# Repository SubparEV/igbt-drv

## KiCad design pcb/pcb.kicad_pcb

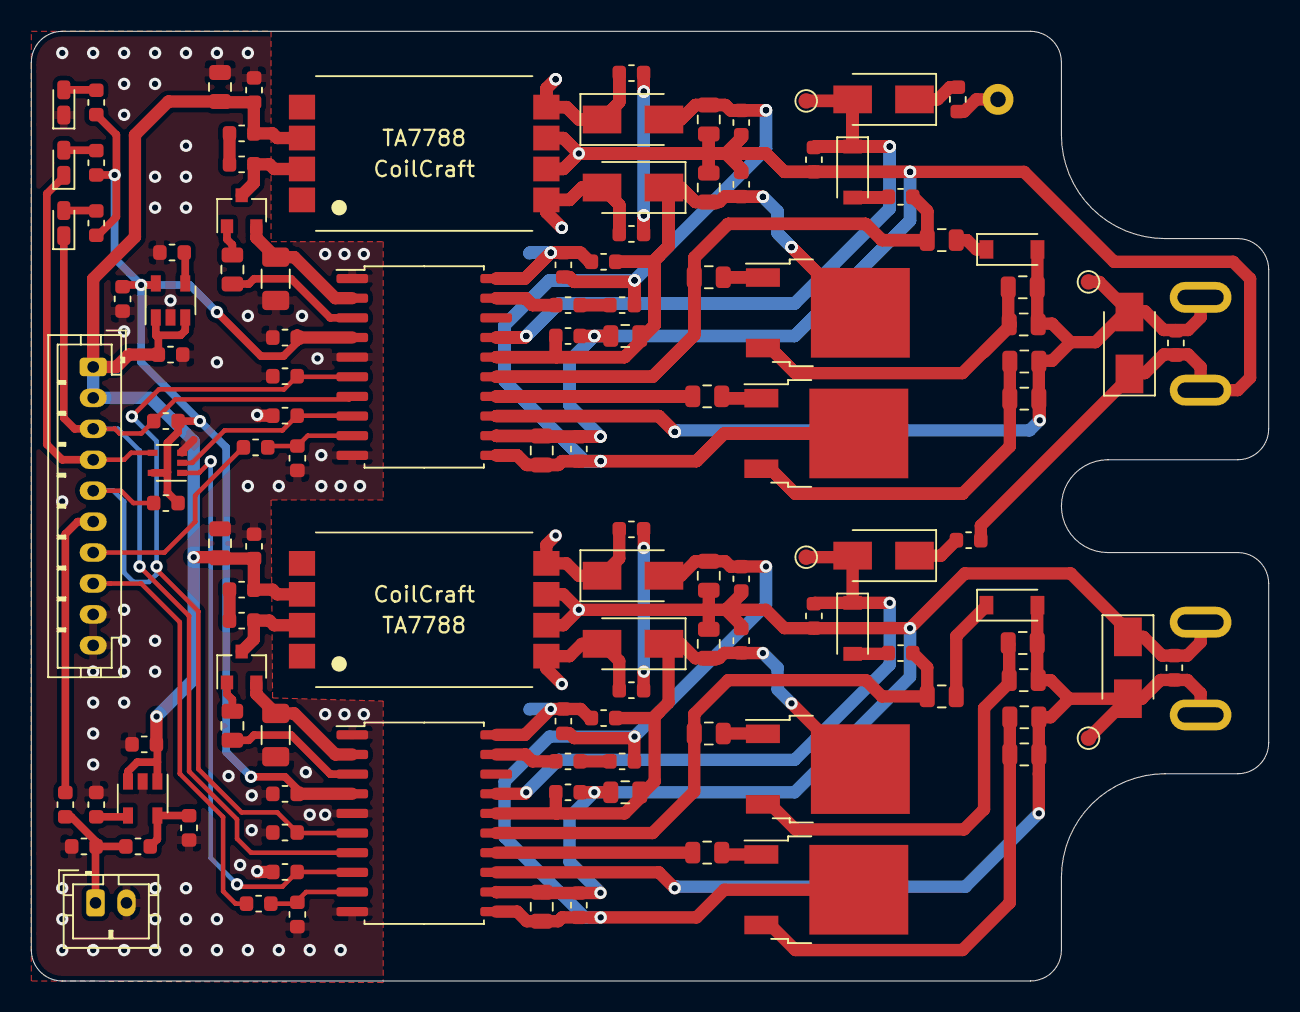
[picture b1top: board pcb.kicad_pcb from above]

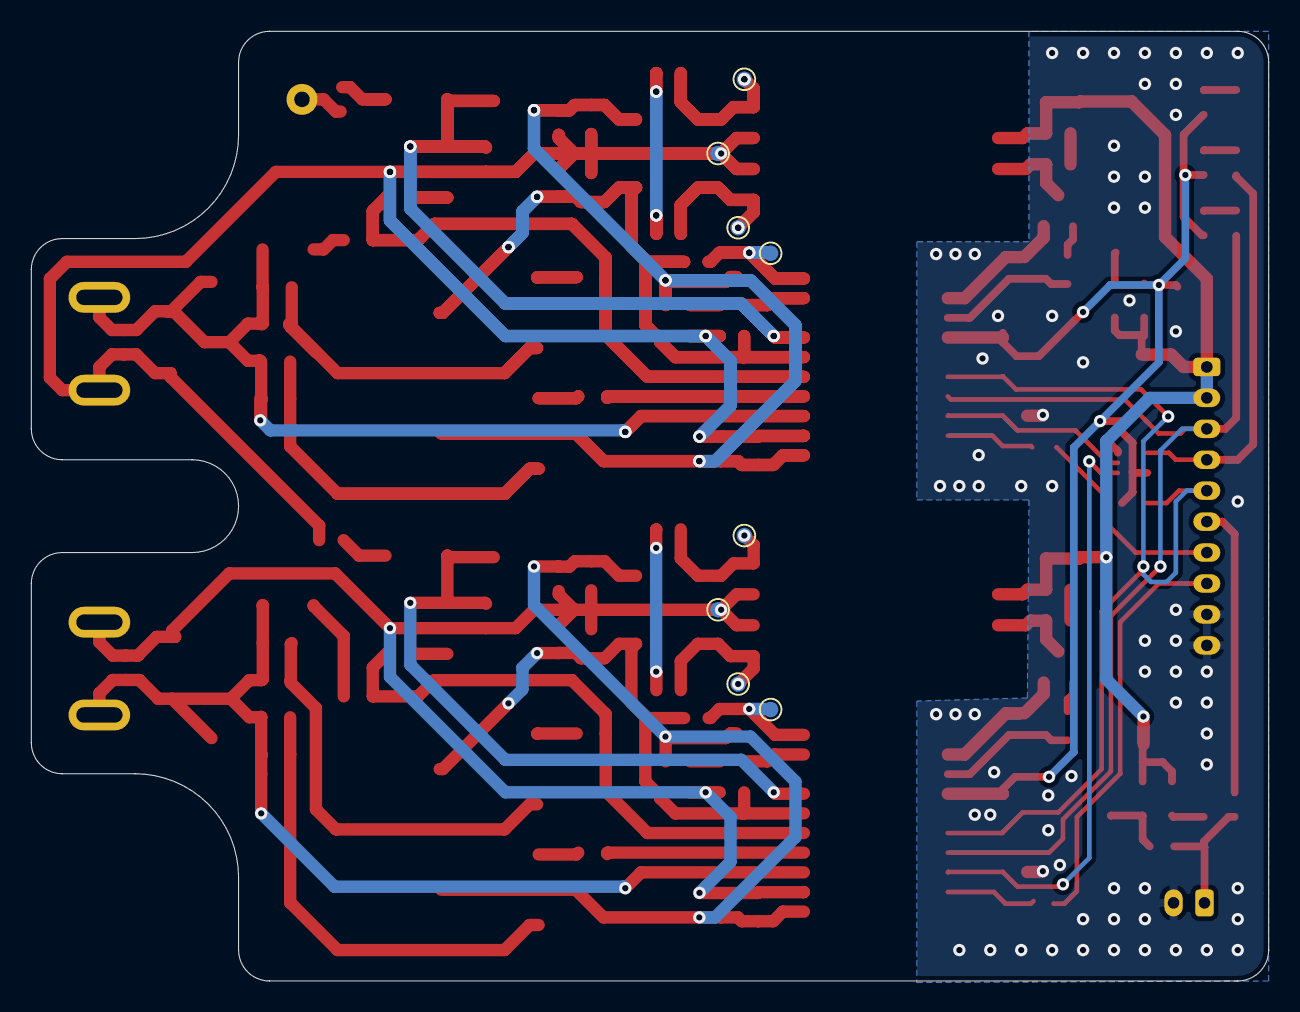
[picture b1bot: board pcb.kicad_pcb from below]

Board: 2 copper layers, 80.0 x 61.4 mm, 133 parts (8 on the bottom side), 71 nets.

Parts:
C1, C3, C4, C8: 2.2uF; C_0603_1608Metric
C2, C7: 470pF; C_0603_1608Metric
C5, C6, C14, C16, C18, C30, C32, C34: 100pF; C_0603_1608Metric
C9, C11, C12, C17, C20, C23, C24, C27, C28, C33, C36, C39, C40: 100nF; C_0603_1608Metric
C10, C15, C19, C21, C22, C26, C31, C35, C37, C38: 10uF; C_0805_2012Metric
C13, C29: 10nF; C_0603_1608Metric
C25, C41: 390pF; C_0603_1608Metric
D1: red; LED_0603_1608Metric_Castellated
D2: green; LED_0603_1608Metric_Castellated
D3: blue; LED_0603_1608Metric_Castellated
D4, D7, D10, D14: B0530W; D_SOD-123
D5, D6, D12, D13: B160; D_SMA
D8, D15: ES1F; D_SMA
D9, D16: SMAJ18CA; D_SMA
J1: Conn_01x10; JST_PH_B10B-PH-K_1x10_P2.00mm_Vertical
J2: Conn_01x02; JST_PH_B2B-PH-K_1x02_P2.00mm_Vertical
J3: Conn_01x01; wire
J4, J5, J6, J7: Conn_01x01; slot
Q1, Q5: Si2302CDS; SOT-23
Q2, Q6: MJD3055T4G; TO-252-2
Q3, Q7: MJD2955T4G; TO-252-2
R1, R2, R5: 220Ω; R_0603_1608Metric
R3, R4, R9, R11, R27, R29, R45: 10kΩ; R_0603_1608Metric
R6, R7, R8, R12, R15, R16, R30, R33, R34: 100Ω; R_0603_1608Metric
R10, R18, R28, R36, R48, R49: 10Ω; R_0805_2012Metric
R13, R31: 100mΩ; R_1206_3216Metric
R14, R32: 182kΩ; R_0603_1608Metric
R17, R35: 8.66kΩ; R_0603_1608Metric
R19, R26, R37, R44: 1kΩ; R_0603_1608Metric
R20, R21, R22, R23, R38, R39, R40, R41: 3Ω; R_0805_2012Metric
R25, R43: 20Ω; R_0805_2012Metric
TP1, TP2, TP3, TP4, TP5, TP6, TP7, TP8, TP9, TP10, TP11, TP12: TestPoint_Alt; TestPoint_Pad_D1.0mm
U1: MIC5205-3.3YM5; SOT-23-5
U2: 74LVC1G08; SOT-353_SC-70-5
U3: MIC5205-5.0YM5; SOT-23-5
U4, U6: Si8282; SOIC-20W_7.5x12.8mm_P1.27mm
U5, U7: TA7788

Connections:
+3V3: C3.1, C12.1, C28.1, R1.1, R2.1, R3.1, R4.1, R5.1, U1.5, U2.5, U4.4, U6.4
+15V: C1.1, C4.1, C10.1, C11.1, C14.1, C26.1, C27.1, C30.1, J1.1, J1.2, U1.1, U1.3, U3.1, U3.3, U5.3, U7.3
/FLT: D1.1, J1.3, R3.2, U4.7, U6.7
/High Side/C: J3.1, R26.2
/High Side/G: D4.2, D9.2, J4.1, R20.2, R21.2, R22.2, R23.2, R27.1, TP6.1, U4.13
/High Side/IN: C5.1, R6.1, U4.9
/High Side/VDDB: C19.1, C20.1, C21.1, C23.1, D5.1, Q2.2, R14.1, U4.16
/High Side/VSSB: C15.2, C16.1, C17.2, C22.2, C24.2, D6.2, Q3.2, R17.2, U4.11
/PWM_H: J1.7, R6.2
/PWM_L: J1.8, R7.2
/RDY: D2.1, J1.4, U2.4
/RDY_B: R29.2, U2.1, U6.8
/RDY_T: R11.2, U2.2, U4.8
/RST: C13.2, C29.2, J1.5, R4.2, U4.6, U6.6
/TEMP: J1.6, R8.1
/sheet5EBDEDF9/C: C15.1, C17.1, C19.2, C20.2, C21.2, C22.1, C23.2, C24.1, C25.2, D9.1, J5.1, R27.2, R44.2, TP2.1, U4.12, U5.6, U5.7
/sheet5EBDEDF9/E: C31.1, C33.1, C35.2, C36.2, C37.2, C38.1, C39.2, C40.1, C41.2, D16.1, J6.1, R45.2, TP8.1, U6.12, U7.6, U7.7
/sheet5EBDEDF9/G: D10.2, D16.2, J7.1, R38.2, R39.2, R40.2, R41.2, R45.1, TP12.1, U6.13
/sheet5EBDEDF9/IN: C6.1, R7.1, U6.9
/sheet5EBDEDF9/VDDB: C35.1, C36.1, C37.1, C39.1, D12.1, Q6.2, R32.1, U6.16
/sheet5EBDEDF9/VSSB: C31.2, C32.1, C33.2, C38.2, C40.2, D13.2, Q7.2, R35.2, U6.11
GND: C1.2, C2.2, C3.2, C4.2, C5.2, C6.2, C7.2, C8.2, C9.2, C10.2, C11.2, C12.2, C13.1, C26.2, C27.2, C28.2, C29.1, D3.1, J1.9, J1.10, J2.2, R11.1, R13.1, R29.1, R31.1, U1.2, U2.3, U3.2, U4.1, U4.5, U4.10, U6.1, U6.5, U6.10
unnamed: C2.1, U1.4
unnamed: C7.1, U3.4
unnamed: C8.1, R9.2, U3.5
unnamed: C9.1, J2.1, R8.2, R9.1
unnamed: C14.2, R12.2
unnamed: C16.2, R15.2
unnamed: C18.1, D5.2, TP1.1, U5.8
unnamed: C18.2, R16.2
unnamed: C25.1, D7.1, D8.2, TP5.1, U4.17
unnamed: C30.2, R30.2
unnamed: C32.2, R33.2
unnamed: C34.1, D12.2, TP7.1, U7.8
unnamed: C34.2, R34.2
unnamed: C41.1, D14.1, D15.2, TP11.1, U6.17
unnamed: D1.2, R1.2
unnamed: D2.2, R2.2
unnamed: D3.2, R5.2
unnamed: D4.1, R25.1
unnamed: D6.1, R16.1, TP3.1, U5.5
unnamed: D7.2, R19.1
unnamed: D8.1, R26.1
unnamed: D10.1, R43.1
unnamed: D13.1, R34.1, TP9.1, U7.5
unnamed: D14.2, R37.1
unnamed: D15.1, R44.1
unnamed: Q1.1, R10.2
unnamed: Q1.2, R13.2, U4.2
unnamed: Q1.3, R12.1, U5.2
unnamed: Q2.1, R18.2
unnamed: Q2.3, R20.1, R21.1
unnamed: Q3.1, R48.2
unnamed: Q3.3, R22.1, R23.1
unnamed: Q5.1, R28.2
unnamed: Q5.2, R31.2, U6.2
unnamed: Q5.3, R30.1, U7.2
unnamed: Q6.1, R36.2
unnamed: Q6.3, R38.1, R39.1
unnamed: Q7.1, R49.2
unnamed: Q7.3, R40.1, R41.1
unnamed: R10.1, U4.3
unnamed: R14.2, R17.1, TP4.1, U4.20
unnamed: R15.1, U4.19
unnamed: R18.1, R19.2, R25.2, U4.15
unnamed: R28.1, U6.3
unnamed: R32.2, R35.1, TP10.1, U6.20
unnamed: R33.1, U6.19
unnamed: R36.1, R37.2, R43.2, U6.15
unnamed: R48.1, U4.14
unnamed: R49.1, U6.14

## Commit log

2020-05-07 pcb: revA proposed
2020-07-30 Finish rev A
